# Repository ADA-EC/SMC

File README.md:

# SMC (Sistema de Monitoramento de Compostagem)
O Sistema de Monitoramento de Compostagem recolhe informações das leiras de temperatura, umidade e nível de metano. 
Esses dados são formatados em tabela e o usuário recolhe estes dados via smartphone com o sistema Android. 
Por ser implementado em local aberto, sem ponto  de energia próximo, o sistema procura ter autonomia energética.

# Sistema ainda em desenvolvimento

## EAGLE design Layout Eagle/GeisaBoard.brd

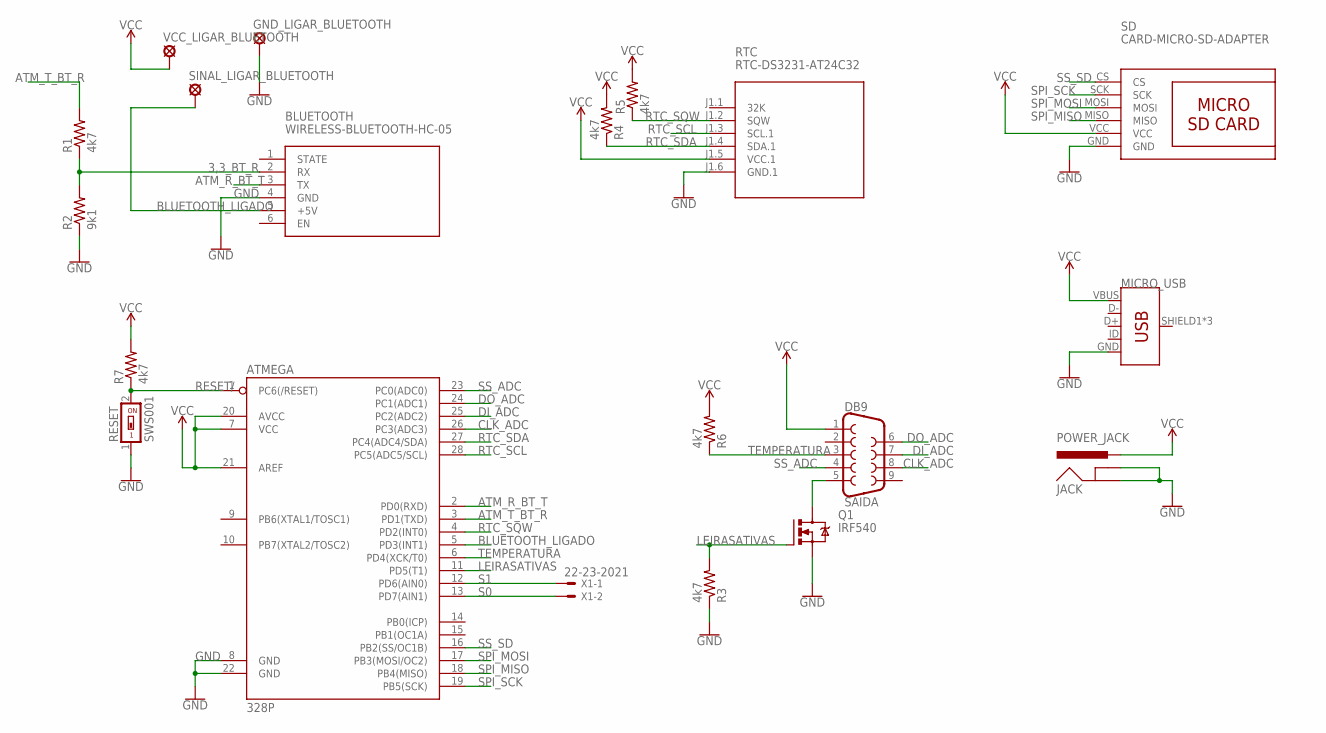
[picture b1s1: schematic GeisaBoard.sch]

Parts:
ATMEGA: 328P; DIP28
BLUETOOTH: WIRELESS-BLUETOOTH-HC-05
DB9: SAIDA; DB9
GND_LIGAR_BLUETOOTH: LSP11
JACK: POWER_JACK; POWER_JACK_PTH
MICRO_USB: USB_MICRO-BREDUCED_PASTE; USB-B-MICRO-SMD_RED_PASTE
Q1: IRF540; TO220BV
R1, R3, R4, R5, R6, R7: 4k7; 0204/7
R2: 9k1; 0204/7
RESET: SWS001; SMS-001
RTC: RTC-DS3231-AT24C32
SD: CARD-MICRO-SD-ADAPTER
SINAL_LIGAR_BLUETOOTH: LSP11
VCC_LIGAR_BLUETOOTH: LSP11
X1: 22-23-2021

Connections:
3,3_BT_R: BLUETOOTH.2 (RX), R1.1, R2.2
ATM_R_BT_T: ATMEGA.2 (PD0(RXD)), BLUETOOTH.3 (TX)
ATM_T_BT_R: ATMEGA.3 (PD1(TXD)), R1.2
BLUETOOTH_LIGADO: ATMEGA.5 (PD3(INT1)), BLUETOOTH.5 (+5V), SINAL_LIGAR_BLUETOOTH.MP
CLK_ADC: ATMEGA.26 (PC3(ADC3)), DB9.8
DI_ADC: ATMEGA.25 (PC2(ADC2)), DB9.7
DO_ADC: ATMEGA.24 (PC1(ADC1)), DB9.6
GND: ATMEGA.8 (GND), ATMEGA.22 (GND), BLUETOOTH.4 (GND), GND_LIGAR_BLUETOOTH.MP, JACK.GND, JACK.GNDBREAK, MICRO_USB.GND, Q1.S, R2.1, R3.1, RESET.1, RTC.J1.6 (GND.1), SD.GND
LEIRASATIVAS: ATMEGA.11 (PD5(T1)), Q1.G, R3.2
unnamed: DB9.5, Q1.D
RESET/: ATMEGA.1 (PC6(/RESET)), R7.1, RESET.2
RTC_SCL: ATMEGA.28 (PC5(ADC5/SCL)), RTC.J1.3 (SCL.1)
RTC_SDA: ATMEGA.27 (PC4(ADC4/SDA)), R4.1, RTC.J1.4 (SDA.1)
RTC_SQW: ATMEGA.4 (PD2(INT0)), R5.1, RTC.J1.2 (SQW)
S0: ATMEGA.13 (PD7(AIN1)), X1.2
S1: ATMEGA.12 (PD6(AIN0)), X1.1
SPI_MISO: ATMEGA.18 (PB4(MISO)), SD.MISO
SPI_MOSI: ATMEGA.17 (PB3(MOSI/OC2)), SD.MOSI
SPI_SCK: ATMEGA.19 (PB5(SCK)), SD.SCK
SS_ADC: ATMEGA.23 (PC0(ADC0)), DB9.4
SS_SD: ATMEGA.16 (PB2(SS/OC1B)), SD.CS
TEMPERATURA: ATMEGA.6 (PD4(XCK/T0)), DB9.3, R6.1
VCC: ATMEGA.7 (VCC), ATMEGA.20 (AVCC), ATMEGA.21 (AREF), DB9.1, JACK.PWR, MICRO_USB.VBUS, R4.2, R5.2, R6.2, R7.2, RTC.J1.5 (VCC.1), SD.VCC, VCC_LIGAR_BLUETOOTH.MP

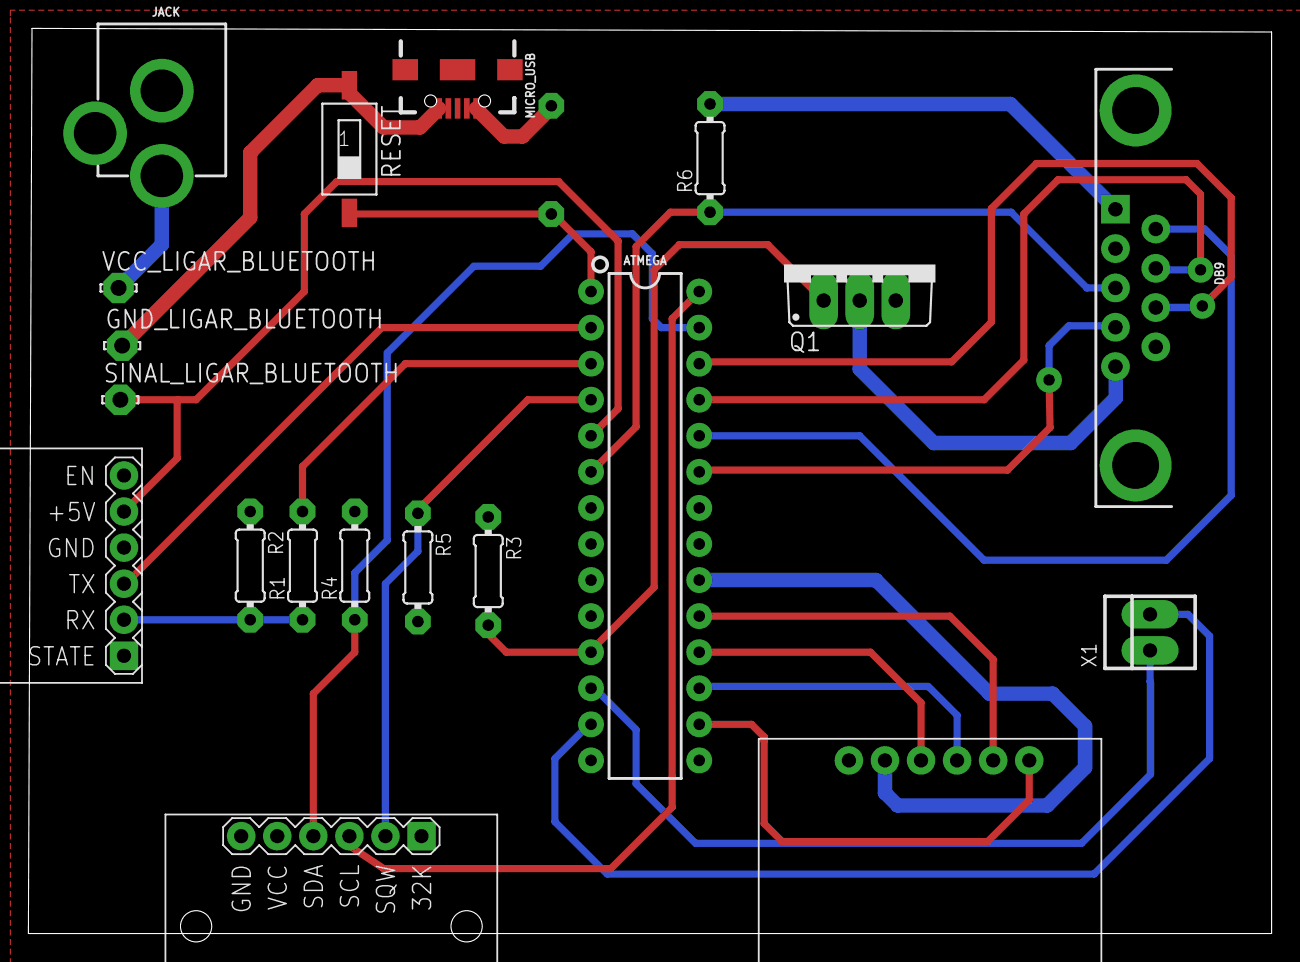
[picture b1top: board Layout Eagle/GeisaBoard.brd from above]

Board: 2 copper layers, 87.6 x 63.7 mm, 20 parts (1 on the bottom side), 23 nets.

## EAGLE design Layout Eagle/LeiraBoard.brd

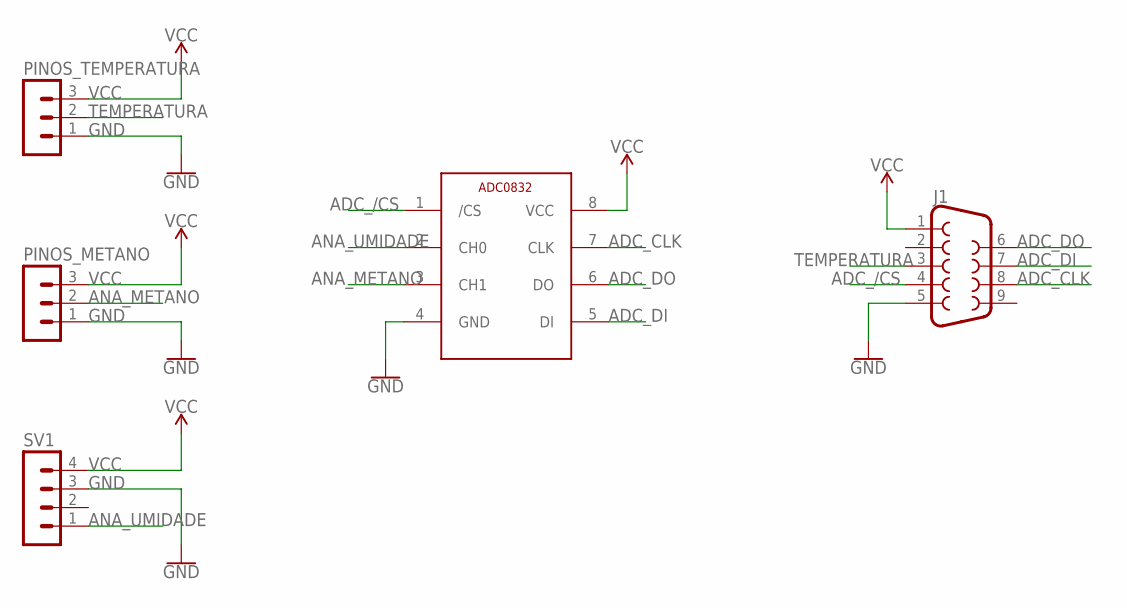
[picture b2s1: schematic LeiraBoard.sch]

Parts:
J1: DB9MALE; DB9_MALE
PINOS_METANO: MA03-1
PINOS_TEMPERATURA: MA03-1
SV1: MA04-1
U$1: ADC8032; DIL8

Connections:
ADC_/CS: J1.4, U$1.1 (/CS)
ADC_CLK: J1.8, U$1.7 (CLK)
ADC_DI: J1.7, U$1.5 (DI)
ADC_DO: J1.6, U$1.6 (DO)
ANA_METANO: PINOS_METANO.2, U$1.3 (CH1)
ANA_UMIDADE: SV1.1, U$1.2 (CH0)
GND: J1.5, PINOS_METANO.1, PINOS_TEMPERATURA.1, SV1.3, U$1.4 (GND)
TEMPERATURA: J1.3, PINOS_TEMPERATURA.2
VCC: J1.1, PINOS_METANO.3, PINOS_TEMPERATURA.3, SV1.4, U$1.8 (VCC)

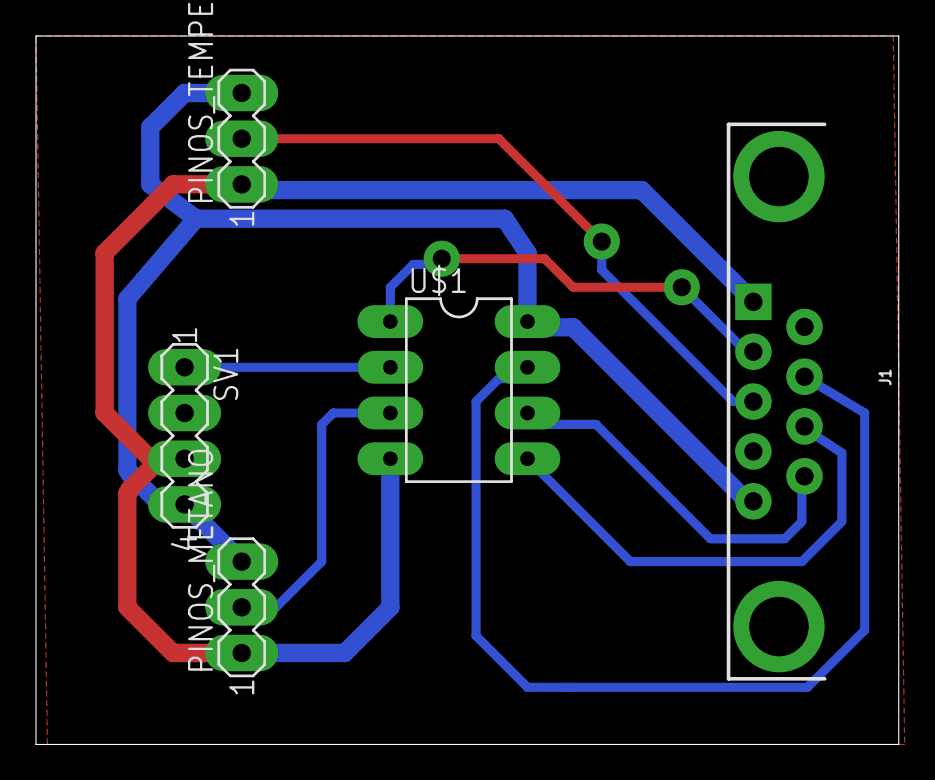
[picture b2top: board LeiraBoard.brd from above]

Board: 2 copper layers, 47.9 x 39.4 mm, 5 parts (0 on the bottom side), 9 nets.

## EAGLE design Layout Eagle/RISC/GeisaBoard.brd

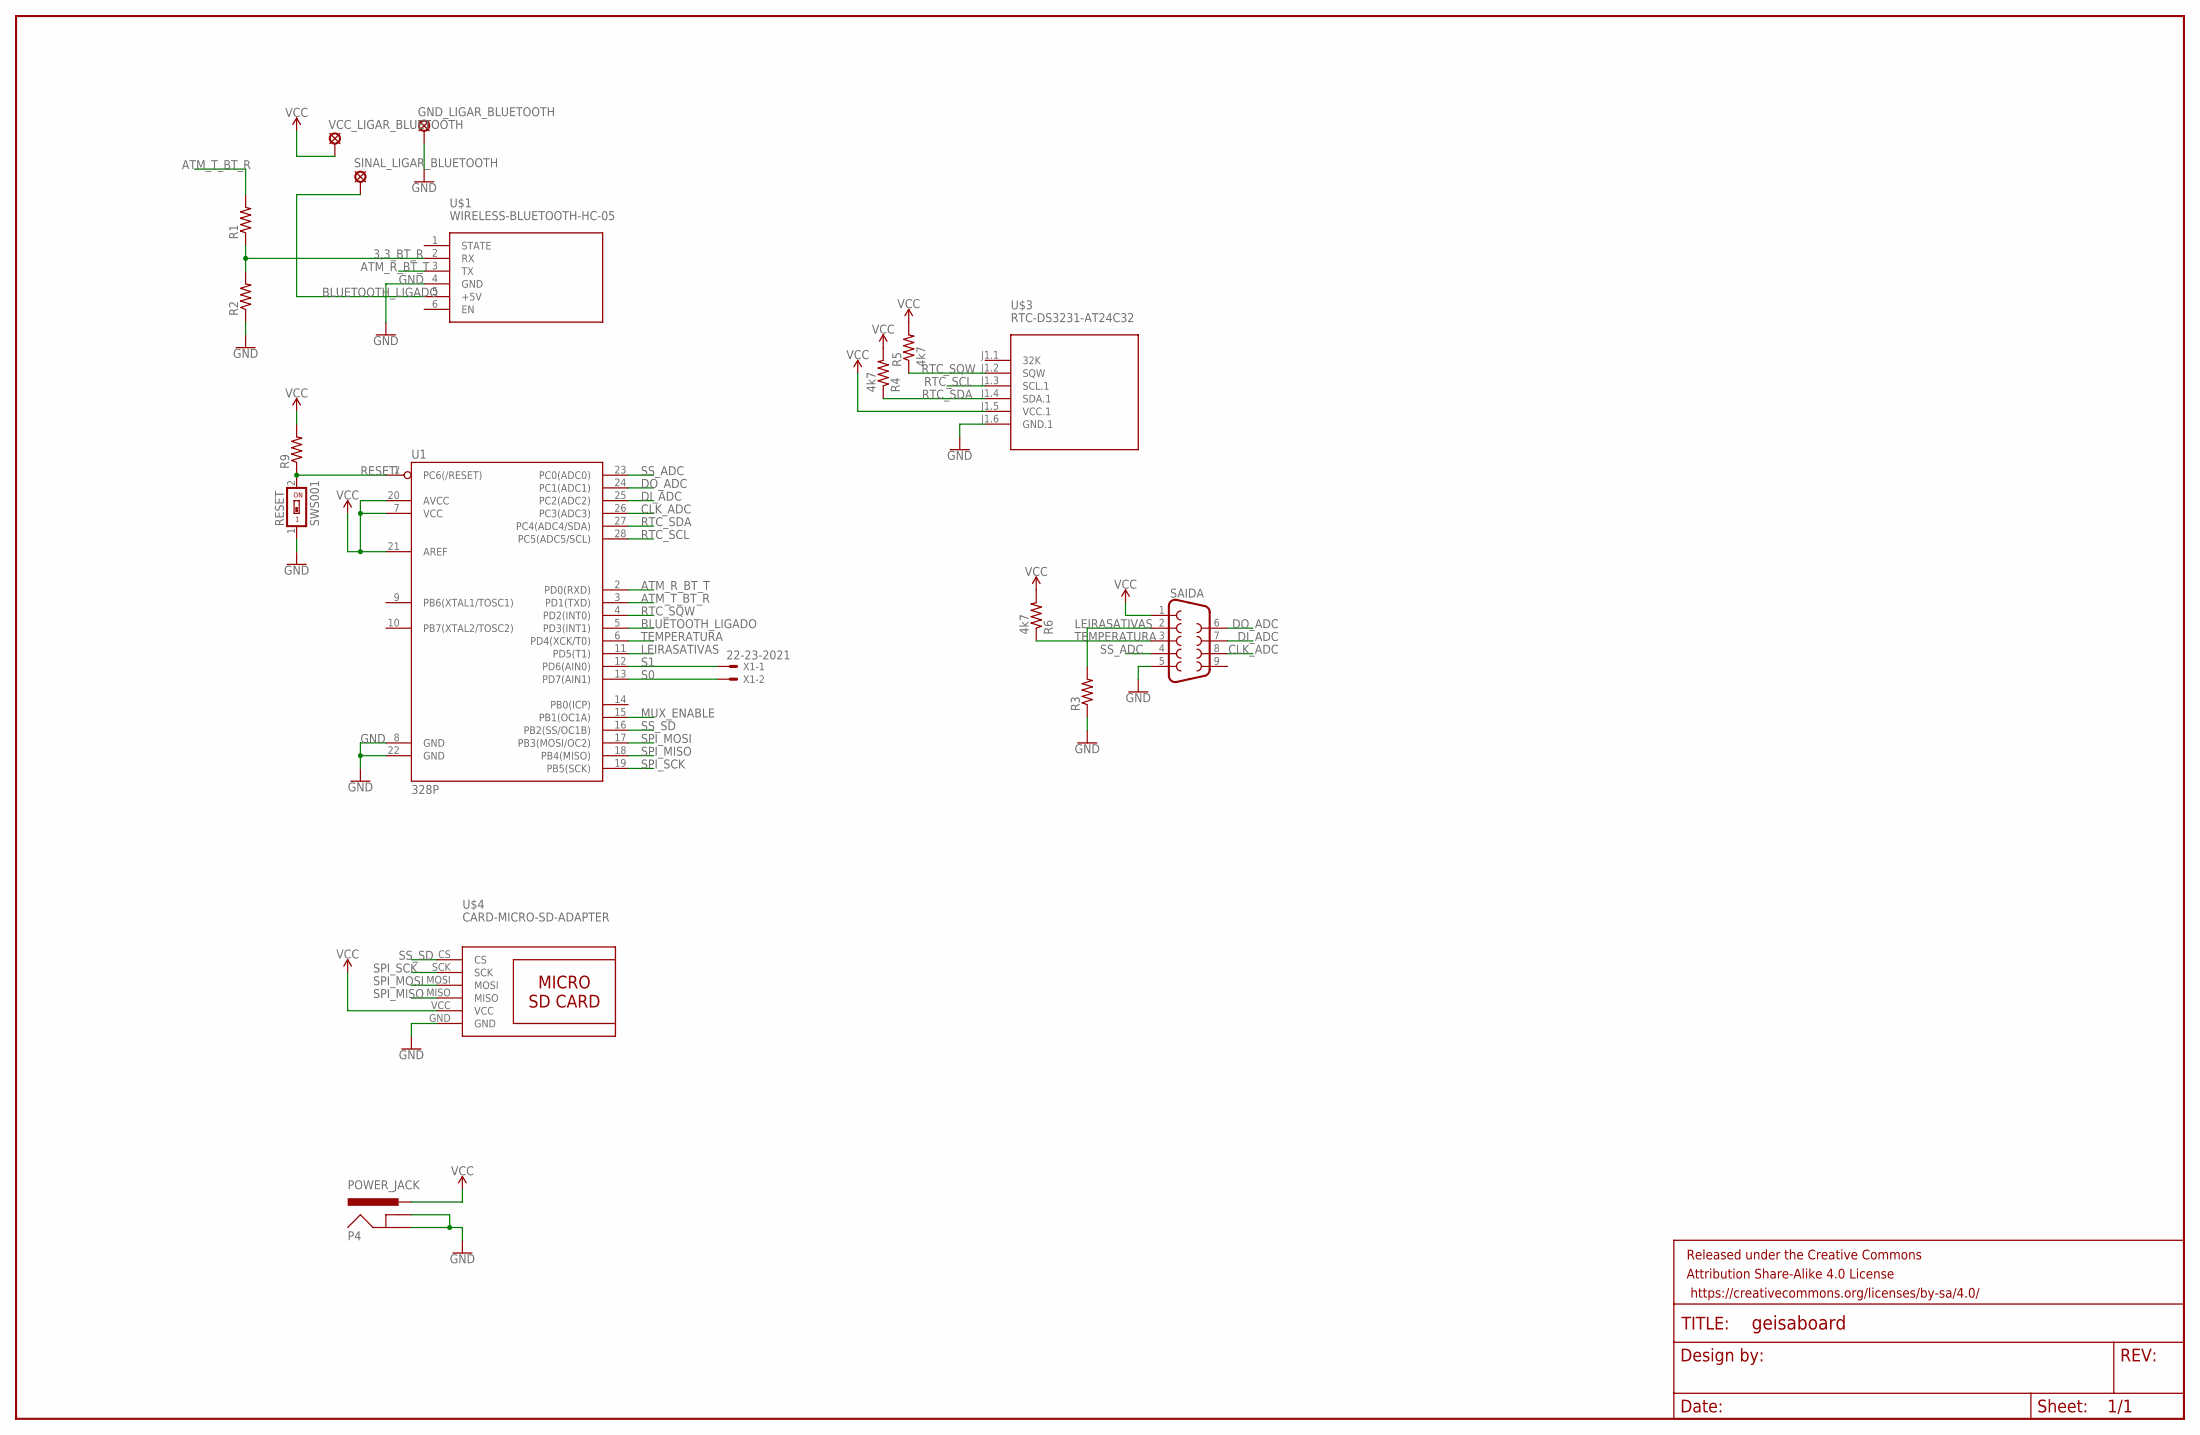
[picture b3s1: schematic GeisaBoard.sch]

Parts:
FRAME1: FRAME-LEDGER; CREATIVE_COMMONS
GND_LIGAR_BLUETOOTH: LSP11
P4: POWER_JACK; POWER_JACK_PTH
R1, R2, R3, R9: R-US_0204/7; 0204/7
R4, R5, R6: 4k7; 0204/7
RESET: SWS001; SMS-001
SAIDA: DB9FEMALE; DB9
SINAL_LIGAR_BLUETOOTH: LSP11
U1: 328P; DIP28
U$1: WIRELESS-BLUETOOTH-HC-05
U$3: RTC-DS3231-AT24C32
U$4: CARD-MICRO-SD-ADAPTER
VCC_LIGAR_BLUETOOTH: LSP11
X1: 22-23-2021

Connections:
3,3_BT_R: R1.1, R2.2, U$1.2 (RX)
ATM_R_BT_T: U1.2 (PD0(RXD)), U$1.3 (TX)
ATM_T_BT_R: R1.2, U1.3 (PD1(TXD))
BLUETOOTH_LIGADO: SINAL_LIGAR_BLUETOOTH.MP, U1.5 (PD3(INT1)), U$1.5 (+5V)
CLK_ADC: SAIDA.8, U1.26 (PC3(ADC3))
DI_ADC: SAIDA.7, U1.25 (PC2(ADC2))
DO_ADC: SAIDA.6, U1.24 (PC1(ADC1))
GND: GND_LIGAR_BLUETOOTH.MP, P4.GND, P4.GNDBREAK, R2.1, R3.1, RESET.1, SAIDA.5, U1.8 (GND), U1.22 (GND), U$1.4 (GND), U$3.J1.6 (GND.1), U$4.GND
LEIRASATIVAS: R3.2, SAIDA.2, U1.11 (PD5(T1))
MUX_ENABLE: U1.15 (PB1(OC1A))
RESET/: R9.1, RESET.2, U1.1 (PC6(/RESET))
RTC_SCL: U1.28 (PC5(ADC5/SCL)), U$3.J1.3 (SCL.1)
RTC_SDA: R4.1, U1.27 (PC4(ADC4/SDA)), U$3.J1.4 (SDA.1)
RTC_SQW: R5.1, U1.4 (PD2(INT0)), U$3.J1.2 (SQW)
S0: U1.13 (PD7(AIN1)), X1.2
S1: U1.12 (PD6(AIN0)), X1.1
SPI_MISO: U1.18 (PB4(MISO)), U$4.MISO
SPI_MOSI: U1.17 (PB3(MOSI/OC2)), U$4.MOSI
SPI_SCK: U1.19 (PB5(SCK)), U$4.SCK
SS_ADC: SAIDA.4, U1.23 (PC0(ADC0))
SS_SD: U1.16 (PB2(SS/OC1B)), U$4.CS
TEMPERATURA: R6.1, SAIDA.3, U1.6 (PD4(XCK/T0))
VCC: P4.PWR, R4.2, R5.2, R6.2, R9.2, SAIDA.1, U1.7 (VCC), U1.20 (AVCC), U1.21 (AREF), U$3.J1.5 (VCC.1), U$4.VCC, VCC_LIGAR_BLUETOOTH.MP

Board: 2 copper layers, 19 parts (1 on the bottom side), 22 nets, no tracks yet.

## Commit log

2017-07-11 Temperature sensor reads data and displays on LCD
2017-07-11 Geisa App
2017-07-19 Interface Changed and New Bluetooth button
2017-07-21 Encontrar e parear com dispositivos
2017-08-01 Bluetooth
2017-08-11 Repository reorganized; RTC lib from third party included but not integrated
2017-08-11 Codigo da main comentado
2017-08-16 tentativa de receber dados
2017-08-16 tentativa de receber dados 2.0
    faltou umas coisas antes
2017-08-18 Um problema no app corrigido
2017-08-23 Sensor de metano/RTC sendo desenvolvidos na proto com LCD
2017-08-25 commit pro mcloving mexer
2017-09-01 novo app
2017-09-29 RTC prototype code written in Arduino for simplicity of development
2017-09-29 Reorganizacao
2017-10-07 Main structure of Integrated code defined. LowPower library adapted from C++ to C code.
2017-10-08 Both interrupts working with power down (RTC int0 and external button int1)
2017-10-14 App com notepad novo
2017-10-16 Bluetooth + Interruptions test code
2017-10-16 Reorganizacao do repositorio
2017-10-16 Neste commit está as coisas do primeiro layout da placa
2017-10-20 Bluetooth sending and reciving from Atmega
2017-10-21 chat
2017-10-21 Library for adc0832; not tested yet
2017-10-25 ADC0832 library tested
2017-10-26 Foram adicionados os arquivos de comando do módulo SD
2017-10-26 Integração com escrita do cartão SD
2017-10-30 Foi feito o arquivo mainExperimental com um começo de main com funções especialistas
2017-10-31 main Experimental foi incrementado e a biblioteca do ds18b20 foi colocada na pasta de integração
2017-11-07 Bluetooth with interrupts
2017-11-07 Bluetooth w/ interrupts integrated but not tested
2017-11-08 RTC set and get date; not tested
2017-11-10 Funções de gravação de medições e leitura de arquivo do SD e transmissão bluetooth terminados
2017-11-10 integração RTC com as funções
2017-11-10 Não testado por problema aleatório na gravação do AtMega
2017-11-24 ADC0832 channel selection
2017-12-06 Bluetooth loop not working properly
2017-12-07 Consegue entrar e sair da rotina do bluetooth. Em teoria a interrupção do RTC também vai funcionar
2017-12-08 Bluetooth and RTC loops working
2017-12-08 Chat changes
2017-12-08 MUX preliminary logic
2017-12-12 Layout atualizado da placa
2017-12-12 SD logic working
2018-03-21 2018
2018-03-21 Logica de selecao de leiras funcionando
2018-04-02 Esquemático corrigido
2018-04-13 Versão inicial do Layout feita
2018-04-14 Layout com correção inicial do Padrão
2018-04-23 Novo layout feito com melhores definições de espessura de trilhas e outros parâmetros
2018-04-24 Posicionamento novo dos componentes
2018-04-25 Layout
2018-04-25 CISC e RISC
2018-05-15 Add BluetoothTerminal Final
    Removi o GeisaApp que não tinha nada funcional e o bluetooth terminal antigo
2018-05-15 Leira Board com esquemático terminado e layout feito
2018-05-16 Alterações na criação do arquivo
2018-05-16 Single leira
2018-05-21 Atualização LeiraBoard
2018-05-21 LeiraBoard Atualizada
2018-05-21 Detalhe do bottom consertado
2018-05-23 README criado
2018-05-24 Teste metano
2018-08-30 Bluetooth Test
2018-09-22 Biblioteca de Eagle do projeto e pdf da LeiraBoard
2018-11-07 Layout GeisaBoard
2018-11-28 GeisaBoard layout completo (espero)
2018-11-29 Resistor de pull-down colocado no chaveamento do transistor de potência
2018-11-30 Versão Final da GeisaBoard
2018-12-04 Valores de resistores colocados
2019-03-04 Atualizações 03-03
2019-03-04 Melhorias nas boas práticas
2019-03-04 Mudanças
2019-03-08 mandatudo para CSV implementado, falta testar

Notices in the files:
parts and their libraries:
SparkFun-IC-Microcontroller: Licensing: Creative Commons ShareAlike 4.0 International - https://creativecommons.org/licenses/by-sa/4.0
diy-modules: Released under the Creative Commons Attribution 4.0 International License: http://creativecommons.org/licenses/by/4.0
